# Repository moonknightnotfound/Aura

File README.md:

# Project AURA

### Ambient Backscatter Communication for Battery-Free Wireless Devices

---

## **Overview**

Ambient backscatter communication enables a device to transmit data without a battery, a power cord, or a dedicated transmitter. While the concept may sound like science fiction, it represents a practical and active area of wireless engineering.

**Project AURA** explores a class of electronics that operate entirely off the grid, communicating using energy "borrowed" from the environment. Rather than generating their own radio waves, AURA devices piggyback on the ambient RF signals already surrounding us — Wi-Fi, television, and cellular transmissions. The principle is analogous to signaling with a mirror: the light is not generated, only reflected, in a controlled and meaningful way.

By making microscopic, deliberate changes to how an antenna reflects incident RF energy, an AURA device is able to encode and transmit data using virtually zero power of its own.

## **What This Project Covers**

Building AURA sits at the intersection of RF engineering, embedded systems, and signal processing. The project involves:

- Designing analog and RF front-end circuitry for signal reflection and modulation
- Programming microcontrollers to drive backscatter modulation in real time
- Capturing, decoding, and analyzing real ambient RF signals
- Investigating near-zero-power techniques that push the limits of low-power wireless design

## **Why It Matters**

Ambient backscatter challenges the conventional assumption that wireless communication requires an active transmitter and a dedicated power source. By demonstrating how information can travel invisibly through existing RF infrastructure, this project establishes a practical path toward self-sustaining, maintenance-free sensor and tag networks.

---

## **Outputs**

### 1. Voltage Multiplier

Design and validation of a voltage multiplier stage for harvesting and stepping up ambient RF energy.

### 2. Survey on FM Signal Strengths

A field survey of ambient FM band signal strength across multiple locations, logging frequency, SNR, and power for each site to identify viable ambient RF sources for backscatter.

### 3. Successful OOK Communication Between Two SDRs

Demonstration of On-Off Keying (OOK) modulation successfully transmitted and received between two software-defined radios.

---

This repository documents the design, hardware, and firmware work behind Project AURA.

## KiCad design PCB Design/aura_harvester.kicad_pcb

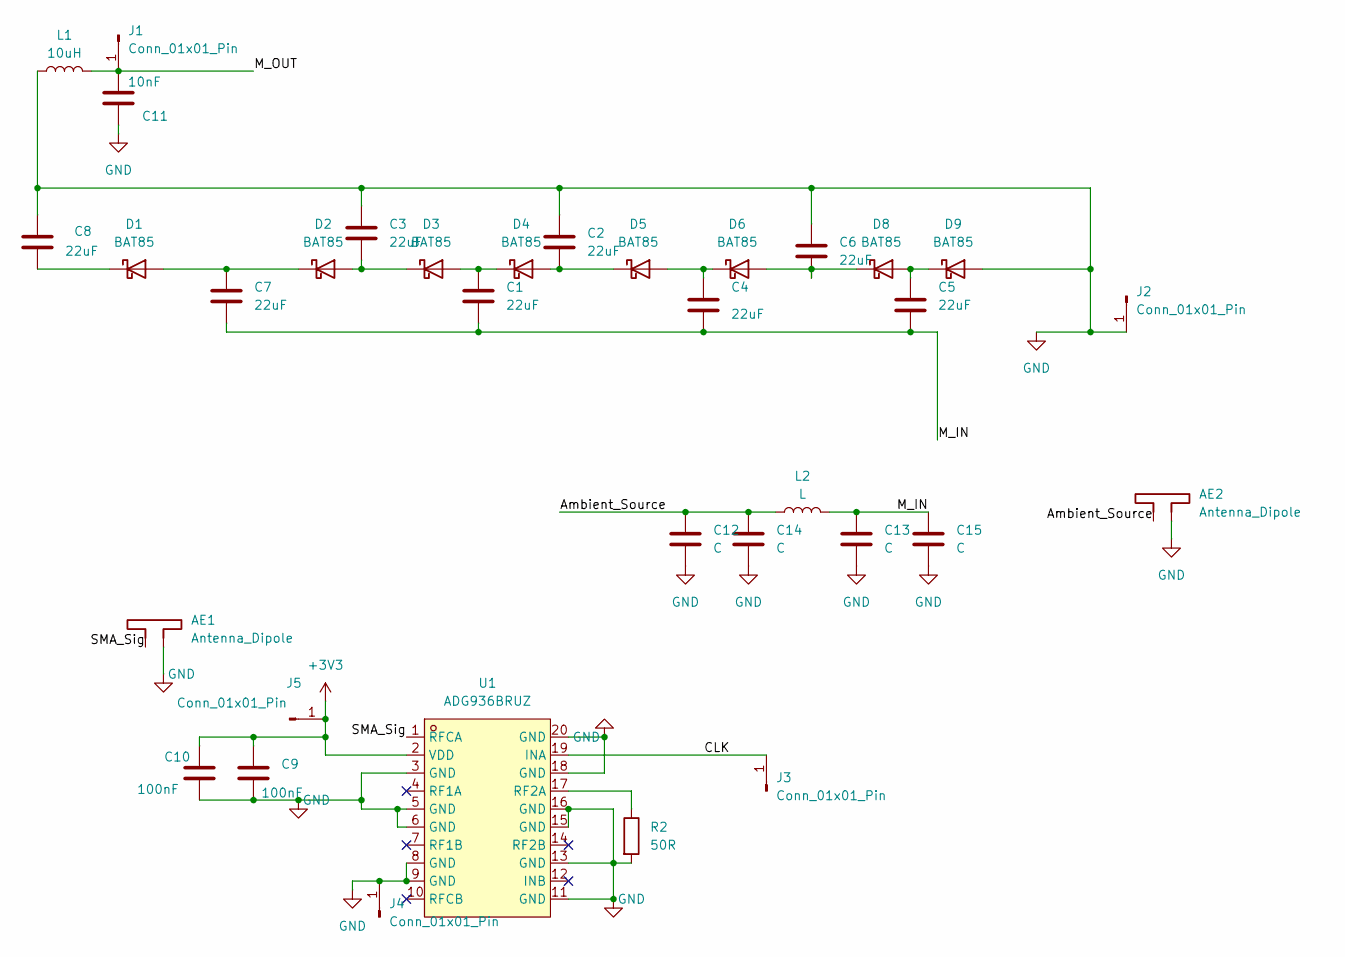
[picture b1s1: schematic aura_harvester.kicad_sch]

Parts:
AE1, AE2: Antenna_Dipole; SMA_Amphenol_132134-10_Vertical
C1, C2, C3, C4, C5, C6, C7, C8: 22uF; C_0805_2012Metric_Pad1.18x1.45mm_HandSolder
C9, C10: 100nF; C_0805_2012Metric_Pad1.18x1.45mm_HandSolder
C11: 10nF; C_0805_2012Metric_Pad1.18x1.45mm_HandSolder
C12, C13, C14, C15: C; C_0805_2012Metric_Pad1.18x1.45mm_HandSolder
D1, D2, D3, D4, D5, D6, D8, D9: BAT85; D_SOD-323_HandSoldering
J1, J2, J3, J4, J5: Conn_01x01_Pin; PinSocket_1x01_P2.54mm_Vertical
L1: 10uH; L_Sunlord_MWSA0603S
L2: L; L_0402_1005Metric_Pad0.77x0.64mm_HandSolder
R2: 50R; R_1206_3216Metric_Pad1.30x1.75mm_HandSolder
U1: ADG936BRUZ; TSSOP-20_ADG936; MPN ADG936BRUZ; LCSC Part C657707

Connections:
+3V3: C9.1, C10.1, J5.1 (Pin_1_1), U1.2 (VDD)
/Ambient_Source: AE2.1, C12.1, C14.1, L2.1
/CLK: J3.1 (Pin_1_1), U1.19 (INA); also elsewhere on the board
/M_IN: C1.2, C4.2, C5.2, C7.2, C13.1, C15.1, L2.2
/M_OUT: C11.2, J1.1 (Pin_1_1), L1.2
/SMA_Sig: AE1.1, U1.1 (RFCA); also elsewhere on the board
GND: AE1.2, AE2.2, C2.1, C3.1, C6.1, C8.1, C9.2, C10.2, C11.1, C12.2, C13.2, C14.2, C15.2, D9.2 (A), J2.1 (Pin_1_1), J4.1 (Pin_1_1), L1.1, R2.2, U1.3 (GND), U1.5 (GND), U1.6 (GND), U1.8 (GND), U1.9 (GND), U1.11 (GND), U1.13 (GND), U1.15 (GND), U1.16 (GND), U1.18 (GND), U1.20 (GND)
unnamed: C7.1, D1.2 (A), D2.1 (K)
unnamed: C8.2, D1.1 (K)
unnamed: C3.2, D2.2 (A), D3.1 (K)
unnamed: C1.1, D3.2 (A), D4.1 (K)
unnamed: C2.2, D4.2 (A), D5.1 (K)
unnamed: C4.1, D5.2 (A), D6.1 (K)
unnamed: C6.2, D6.2 (A), D8.1 (K)
unnamed: C5.1, D8.2 (A), D9.1 (K)
unnamed 15: U1.4 (RF1A); also elsewhere on the board
unnamed 16: R2.1, U1.17 (RF2A); also elsewhere on the board

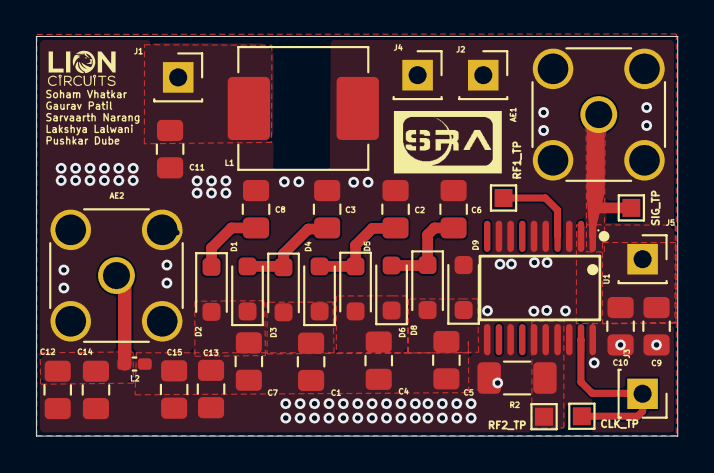
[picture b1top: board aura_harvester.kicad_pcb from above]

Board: 2 copper layers, 35.6 x 22.2 mm, 38 parts (0 on the bottom side), 17 nets.

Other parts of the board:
CLK_TP: CLK_TP; TestPoint_Pad_1.0x1.0mm
RF1_TP: RF1_TP; TestPoint_Pad_1.0x1.0mm
RF2_TP: RF_TP; TestPoint_Pad_1.0x1.0mm
SIG_TP: SIG_TP; TestPoint_Pad_1.0x1.0mm

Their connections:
/CLK: CLK_TP.1 (1_1); also elsewhere on the board
/SMA_Sig: SIG_TP.1 (1_1); also elsewhere on the board
unnamed 15: RF1_TP.1 (1_1); also elsewhere on the board
unnamed 16: RF2_TP.1 (1_1); also elsewhere on the board

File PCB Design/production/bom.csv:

Designator,Footprint,Quantity,Value,LCSC Part #
"AE1, AE2",SMA_Amphenol_132134_Vertical,2,Antenna_Dipole,
"C1, C2, C3, C4, C5, C6, C7, C8",0805,8,22uF,
"C10, C9",0805,2,100nF,
C11,0805,1,10nF,
"C12, C13, C14, C15",0805,4,C,
CLK_TP,TestPoint_Pad_1.0x1.0mm,1,CLK_TP,
"D1, D2, D3, D4, D5, D6, D8, D9",D_SOD-323_HandSoldering,8,BAT85,
"J1, J2, J3, J4, J5",PinSocket_1x01_P2.54mm_Vertical,5,Conn_01x01_Pin,
L1,L_Sunlord_MWSA0603S,1,10uH,
L2,0402,1,L,
R2,1206,1,50R,
RF1_TP,TestPoint_Pad_1.0x1.0mm,1,RF1_TP,
RF2_TP,TestPoint_Pad_1.0x1.0mm,1,RF_TP,
SIG_TP,TestPoint_Pad_1.0x1.0mm,1,SIG_TP,
U1,TSSOP-20_ADG936,1,ADG936BRUZ,C657707
